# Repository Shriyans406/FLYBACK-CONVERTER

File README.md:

# Active-Clamp Flyback Converter (400 V → 54 V / 1 A)

Everything for this project lives in this one folder. There is one copy of each file.

## 1. What is where

| Path | What it is |
|---|---|
| `11-07-26.asc` | **The final LTspice design** (active-clamp flyback, closed loop) |
| `11-07-26.plt` | Plot layout LTspice loads automatically for that file |
| `11-07-26_RCD_original.asc` | Your original RCD-snubber version, kept as the only backup of it |
| `ACF_verification.png` | Waveform plots from the verified simulation |
| other `.asc` / `Draft*` files | Your earlier internship iterations (untouched) |
| `pcb/ACF_Flyback.kicad_pro` | **KiCad project — open this one** |
| `pcb/ACF_Flyback.kicad_sch` | Schematic |
| `pcb/ACF_Flyback.kicad_pcb` | Routed 2-layer board |
| `pcb/ACF_Flyback.kicad_dru` | High-voltage spacing rules used by the design-rule check |
| `pcb/ACF.kicad_sym`, `pcb/sym-lib-table` | Schematic symbols used by this project |
| `pcb/design.py` | **The single source of truth**: parts, values, positions, nets, spacing rules, copper pours |
| `pcb/gen_schematic.py`, `build_1_place.py`, `route.py`, `build_3_finish.py`, `make_bom.py` | Scripts that turn `design.py` into the schematic, board and BOM |
| `pcb/build_all.bat` | Runs all of the above in order |
| `pcb/check_netlist.py` | Cross-checks the schematic netlist against `design.py` |
| `pcb/pads.json`, `pcb/routes.json` | Intermediate data passed between the build scripts |
| `pcb/fab/gerbers/` | Gerber + drill files for the PCB manufacturer |
| `pcb/fab/ACF_Flyback_BOM.csv` | Bill of materials |
| `pcb/fab/ACF_Flyback_CPL.csv` | Pick-and-place (component position) file |
| `pcb/fab/ACF_Flyback_schematic.pdf` | Schematic as a PDF |
| `pcb/fab/DRC_report.txt`, `ERC_report.txt` | Board and schematic check reports |
| `pcb/renders/top.png`, `bottom.png` | 3D renders of the board |

### Usability features on the board (converter values unchanged)

| Feature | Where | What it is for |
|---|---|---|
| **HV LIVE** red LED (`D3`, `R26`–`R28`) | primary, left of centre | Lit while the bulk capacitor is charged. Do not touch the board until it goes out. Draws about 0.6 mA from the 400 V rail. |
| **BIAS** yellow LED (`D4`, `R25`) | next to the 12 V header | Shows the controller supply is present. |
| **OUTPUT ON** green LED (`D5`, `R24`) | secondary, lower right | Shows 54 V is present. Draws about 2 mA. |
| Probe loops `TP1` VOUT, `TP2` RTN | secondary, lower right | Clip a multimeter or scope here to measure the output safely. |
| Probe points `TP3` VCC, `TP4` PGND, `TP5` CS, `TP6` GATE | primary | Debug points. **These are on the live side: use an isolated or differential probe.** |
| Silkscreen legends | at every connector, LED and test point | Polarity (`+400V`/`GND`, `+54V`/`RTN`), fuse rating, bias pin order, and a discharge warning. |
| Rounded corners (3 mm) | board outline | Safer handling, easier fit in a case. |
| Fiducials `FID1`–`FID3` | three corners | Alignment marks for machine assembly. |
| Enclosure | `pcb/enclosure/` | 163 × 108 × 51 mm tray with stand-offs under the four M3 holes, wire openings at both terminal blocks and the bias header, and a flat lid. |

Enclosure files: `ACF_enclosure_base.wrl` / `_lid.wrl` are what KiCad's 3D viewer shows; `ACF_enclosure_base.stl` / `_lid.stl` are the same shapes in millimetres for CAD or 3D printing. `gen_enclosure.py` creates them from the `ENC` settings in `design.py`.

To see the enclosure in KiCad: open the board, press **Alt+3**. The base is shown; the lid is hidden so it does not cover the board. To show the lid, double-click footprint `ENC2` (select it via **Edit → Find**, search `ENC2`), go to the **3D Models** tab and tick **Show**. To hide the whole case, untick **Show** on `ENC1` the same way. The case outline is also drawn on the `User.Drawings` layer.

## 2. How to view everything

### LTspice simulation
1. Double-click `11-07-26.asc` (opens in LTspice).
2. Press the **Run** button (running man). The run takes about 2 minutes.
3. Four plots appear automatically: `V(out)`, `V(ds)`, `I(L1)`, and duty/soft-start.
4. Click any wire to plot its voltage; click a component to plot its current.
5. **View → SPICE Output Log** (Ctrl+L) shows the measured numbers: output voltage, ripple, efficiency, duty, peak `V(ds)`, and `V(ds)` at turn-on (the zero-voltage-switching check).
6. To see zero-voltage switching: zoom into the last few cycles and plot `V(ds)` together with `V(gs)`.

The `.raw` result file is about 430 MB, so it was deleted to save space. LTspice recreates it each time you press Run.

### KiCad schematic and board
1. Open **KiCad**, then **File → Open Project** and pick `pcb/ACF_Flyback.kicad_pro`.
2. Double-click the schematic file to open the **Schematic Editor**. The sheet is split into six numbered sections. Every pin carries a net label instead of drawn wires; pins with the same label are connected. Click a label and press **`** (backtick) to highlight that net.
3. Double-click the board file to open the **PCB Editor**.
   - **View → 3D Viewer** (Alt+3) shows the board in 3D.
   - Use the layer list on the right to show only `F.Cu` (top copper) or `B.Cu` (bottom copper).
   - Click any pad or track and press **`** to highlight its whole net.
   - **Inspect → Design Rules Checker → Run DRC** re-runs the check. Tick "Test for parity between PCB and schematic" to compare against the schematic.
4. Manufacturing files: in the KiCad project window choose **Gerber Viewer**, then **File → Open Gerber Job File** and pick `pcb/fab/gerbers/ACF_Flyback-job.gbrjob`. Then **File → Open Excellon Drill File** and pick `ACF_Flyback.drl`.
5. `BOM.csv` and `CPL.csv` open in Excel. The PDF and PNG files open with any viewer.

## 3. How to change things

### LTspice
- Right-click a component to change its value; right-click a blue text line to edit a directive.
- Useful knobs: `C1` (output capacitor), `L1`/`L2` (transformer, keep the 100:1 inductance ratio for 10:1 turns), `Cclamp`, `R2`/`C2`/`C3` (compensator), `Vss` (soft-start ramp), `Istep` (load step; delete it for a plain steady-state run).
- `.options reltol=0.001` gives clean waveforms. Changing it to `0.01` runs about 3× faster but adds a fake low-frequency wobble.

### PCB — two ways, do not mix them
**A. Edit by hand in KiCad** (best for small moves or re-routing):
edit the schematic or board in KiCad and save. Then use **Tools → Update PCB from Schematic** as normal.
Do **not** run `build_all.bat` afterwards — it regenerates the files and overwrites hand edits.

**B. Edit `pcb/design.py` and regenerate** (best for changing parts, values, positions or spacing rules):
1. Close KiCad (it locks the files).
2. Open `pcb/design.py` in any text editor.
   - `PARTS` — one line per component: footprint, value, x/y position in mm, rotation, and which pad goes to which net.
   - `clearance()` — the spacing rules between voltage domains.
   - `POURS` — the copper pour rectangles.
   - `TRACK_W` — track widths per net.
3. Double-click `pcb/build_all.bat`. It takes about 2 minutes.
4. Read `pcb/fab/DRC_report.txt` and `pcb/fab/ERC_report.txt`, then open the project in KiCad to look.

If the router prints `FAILED` for a net, two parts are too close for the spacing rules: move one of them in `PARTS` and run again.

## 4. How it was built

### Simulation
1. Read the internship report and the original `11-07-26.asc` (RCD-snubber flyback).
2. Replaced the RCD snubber with an active clamp (clamp MOSFET `M2` + `Cclamp`), driven complementary to `M1` with 0.5 µs dead-time.
3. Raised the transformer inductance from 572 µH to 25 mH so the magnetising current swings negative each cycle. That is what gives zero-voltage switching and removes the idle period that caused ringing.
4. Replaced the generic MOSFET with a model of the Infineon IMBF170R1K0M1, fitted to its datasheet values.
5. Recalculated the output capacitor for the new operating point (180 µF) and retuned the compensator.
6. Added a duty soft-start and an anti-windup clamp on the error amplifier.
7. Ran LTspice in batch mode after each change and read the `.meas` results until output voltage, ripple, zero-voltage switching and a load step all checked out.

### PCB
1. Chose real parts for what LTspice modelled as ideal blocks: LM5025 controller, UCC5350 isolated high-side driver with bootstrap diode, TL431 + optocoupler feedback, fuse, bulk capacitor, Y capacitor.
2. Wrote the whole design as data in `design.py`.
3. `build_1_place.py` (KiCad's Python) creates the board outline and isolation slots and places every footprint from the KiCad libraries.
4. `route.py` is a grid router written for this board. It routes each net on a 0.1 mm grid and keeps the spacing each voltage domain needs.
5. `build_3_finish.py` adds the tracks, vias, thermal vias, copper pours and bottom-side high-voltage keep-outs, fills the zones, and writes the DRC rule file.
6. `gen_schematic.py` writes the schematic from the same data, so the schematic and board cannot disagree.
7. KiCad's own checks were then run from the command line: DRC with schematic parity, and ERC. Result: 0 errors, 0 unconnected nets, 0 parity issues, 14 silkscreen warnings.
8. Gerbers, drill, placement, BOM, PDF and renders were exported with `kicad-cli`.

## 5. Known limits — read before ordering boards

- **Transformer footprint is a placeholder** (library ETD29 bobbin). A 25 mH, 10 kHz transformer needs a larger core; replace the footprint once the transformer is designed.
- **10 kHz is unusually low for the LM5025**; check its oscillator range or raise the switching frequency.
- **MOSFET footprint is the generic TO-263-7 pattern**; check it against Infineon's package drawing.
- **Spacing values are engineering choices** (8 mm primary-to-secondary, 3 mm around 1 kV nets, 2.5 mm around 400 V), not checked against a specific safety standard. 3 mm at 1 kV assumes conformal coating.
- **The TL431/optocoupler loop values are starting points**; that loop was not simulated.
- **Pin assumptions to check on datasheets:** LM5025 VIN tied to VCC for 12 V operation; TL431 pin order for the vendor you buy.
- **The BOM has no manufacturer part numbers for passives**, and the placement file includes through-hole parts.
- **Controller bias is an external 12 V header**, not an auxiliary winding.
- **The enclosure is a concept model.** It is plain blocks: no screw holes in the stand-offs, no lid fixings, no vents, and its 38 mm inner height has not been checked against a real transformer. The STL files are overlapping solids and have not been test-printed. Choose a flame-rated insulating material for a 400 V product.
- **The two indicator LEDs on the power rails add small loads** (about 0.6 mA at 400 V and 2 mA at 54 V); these were not added to the LTspice model.

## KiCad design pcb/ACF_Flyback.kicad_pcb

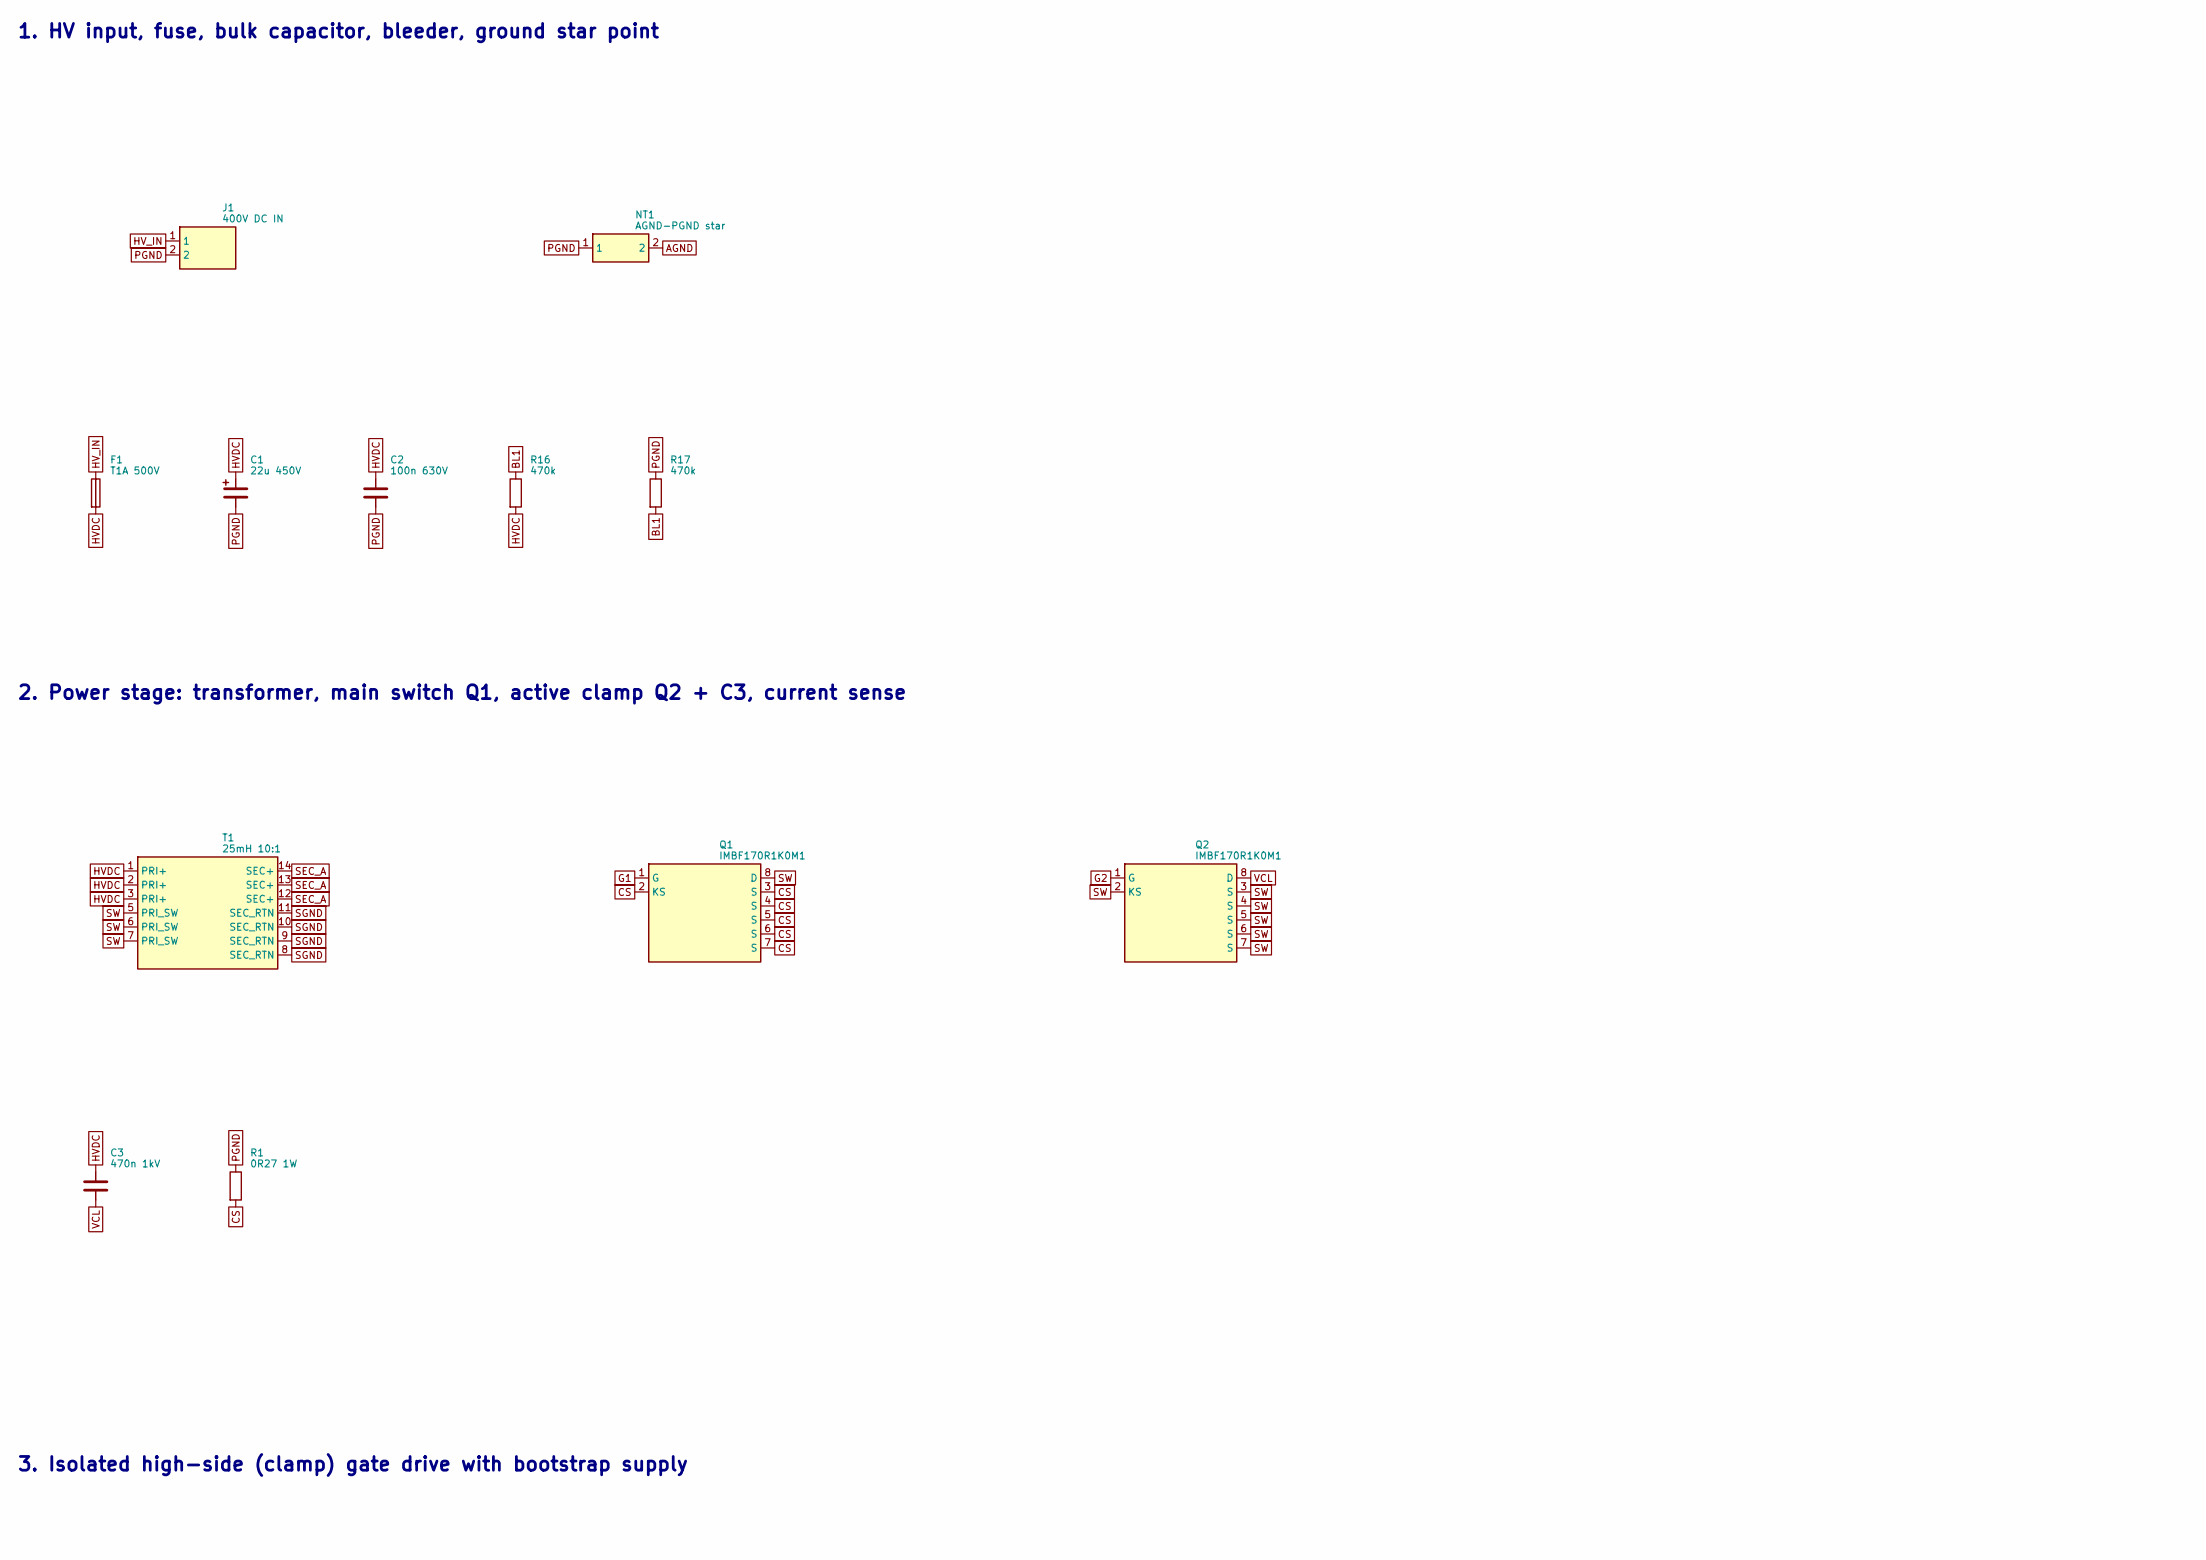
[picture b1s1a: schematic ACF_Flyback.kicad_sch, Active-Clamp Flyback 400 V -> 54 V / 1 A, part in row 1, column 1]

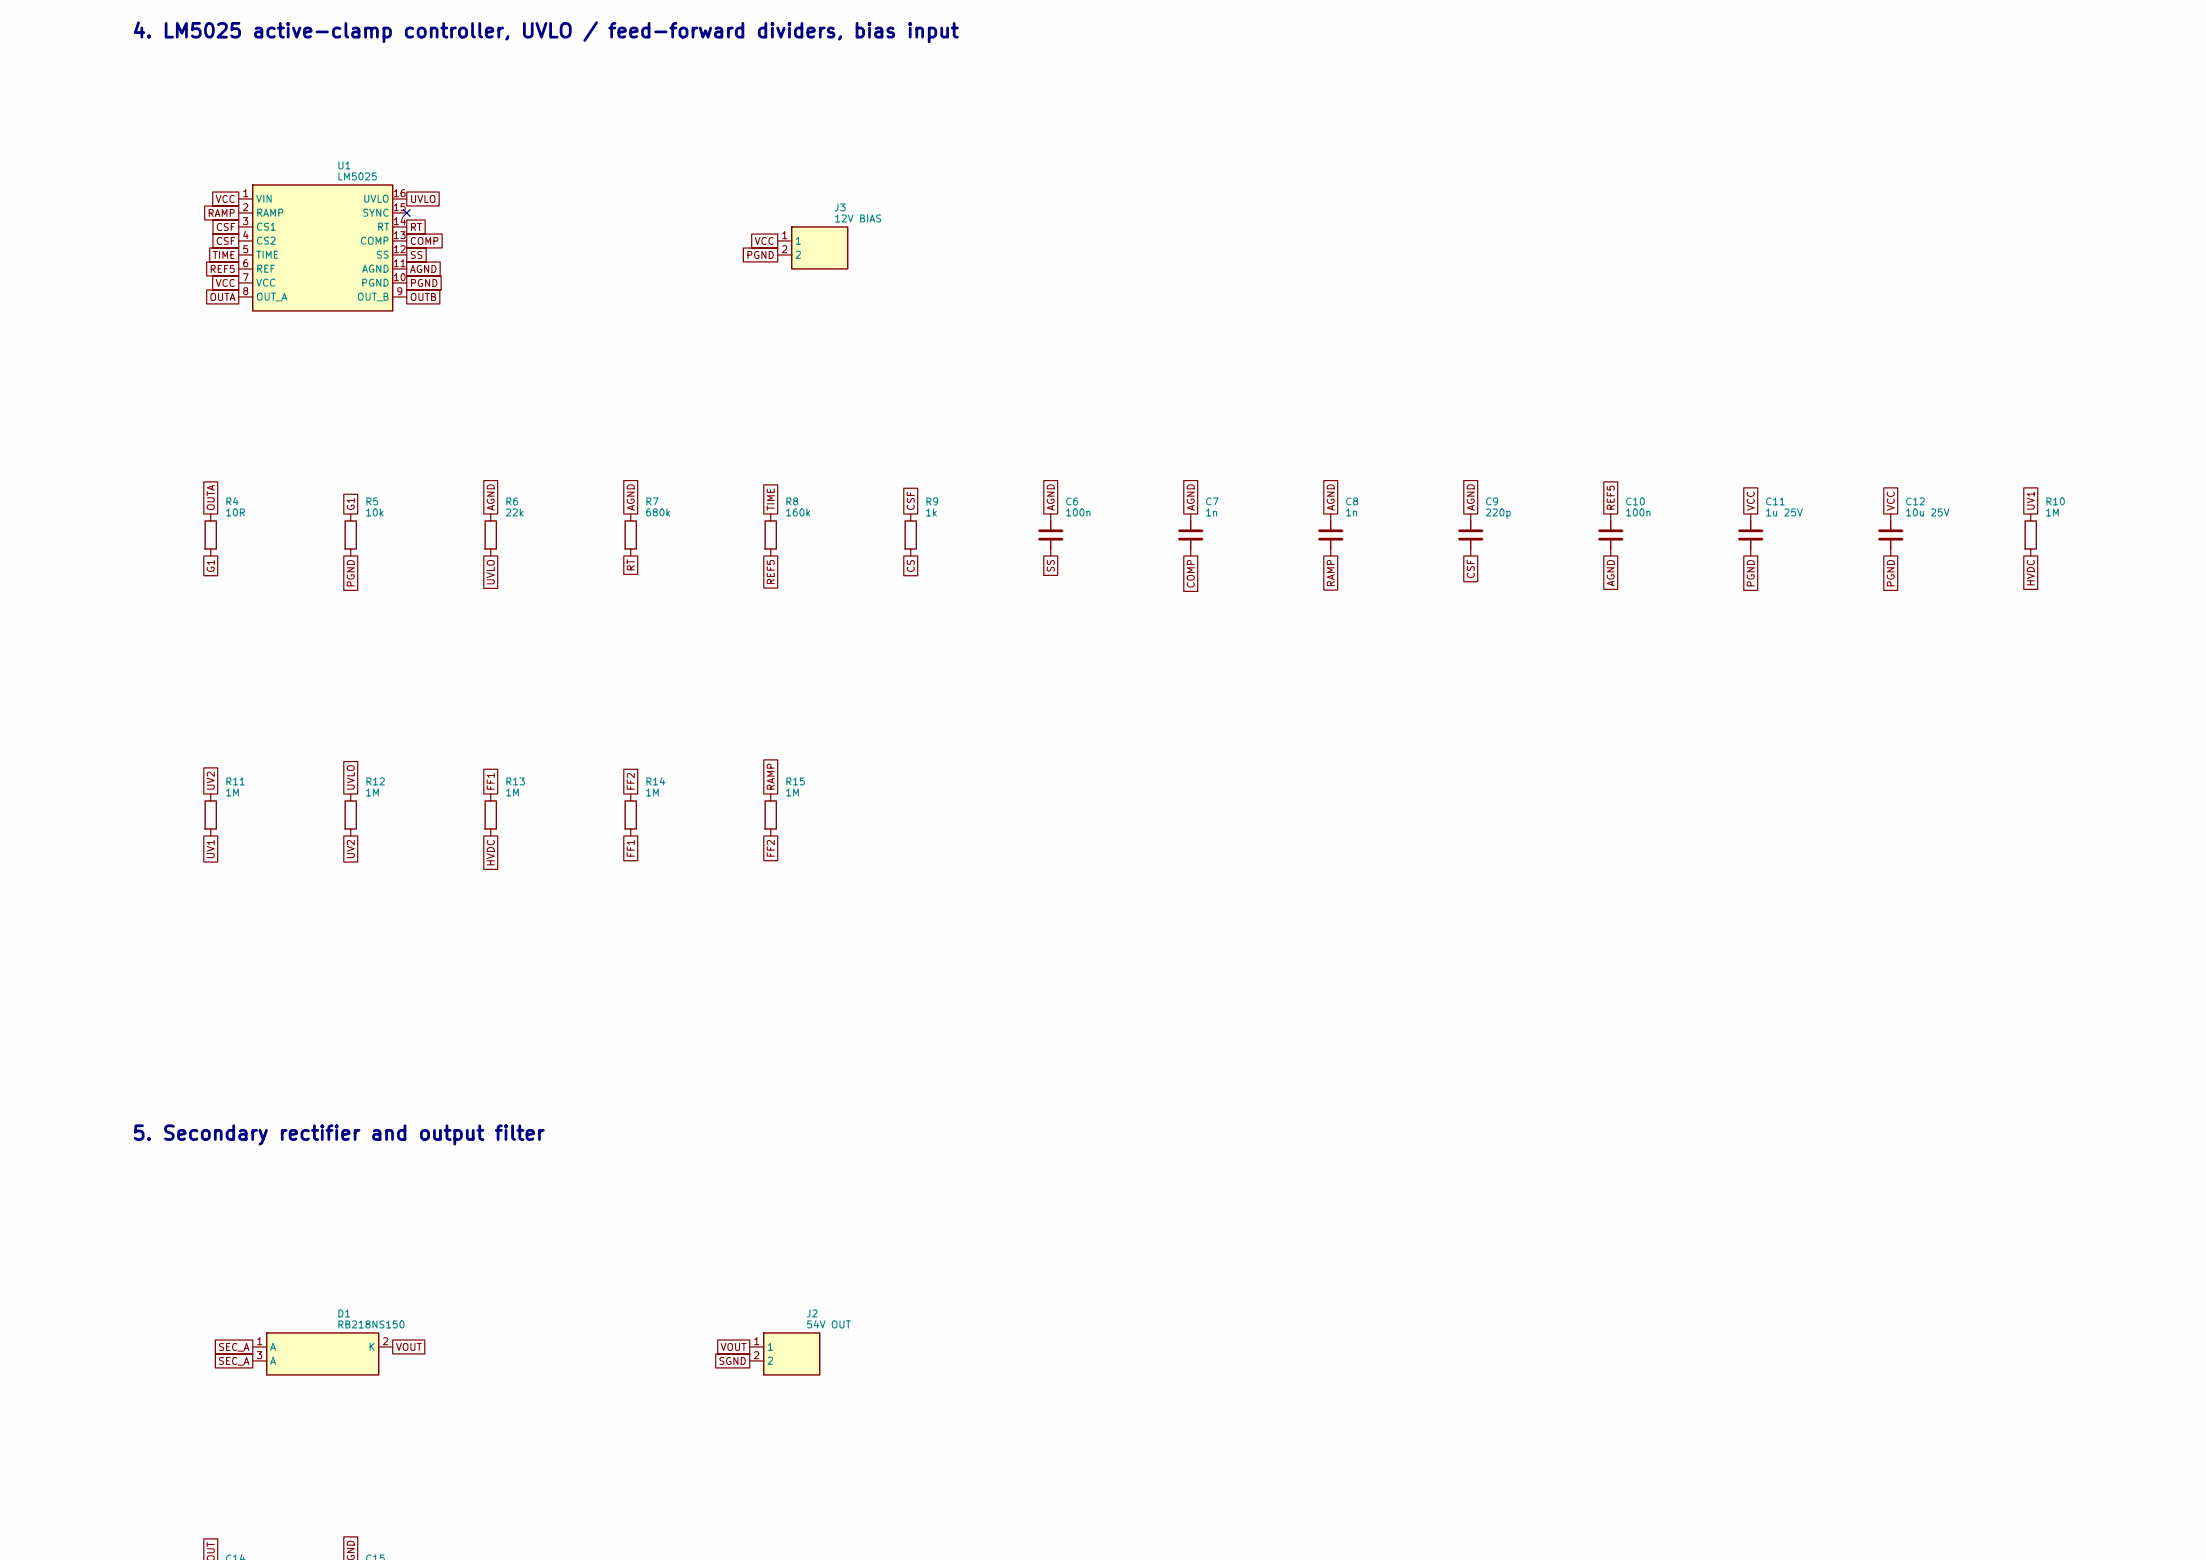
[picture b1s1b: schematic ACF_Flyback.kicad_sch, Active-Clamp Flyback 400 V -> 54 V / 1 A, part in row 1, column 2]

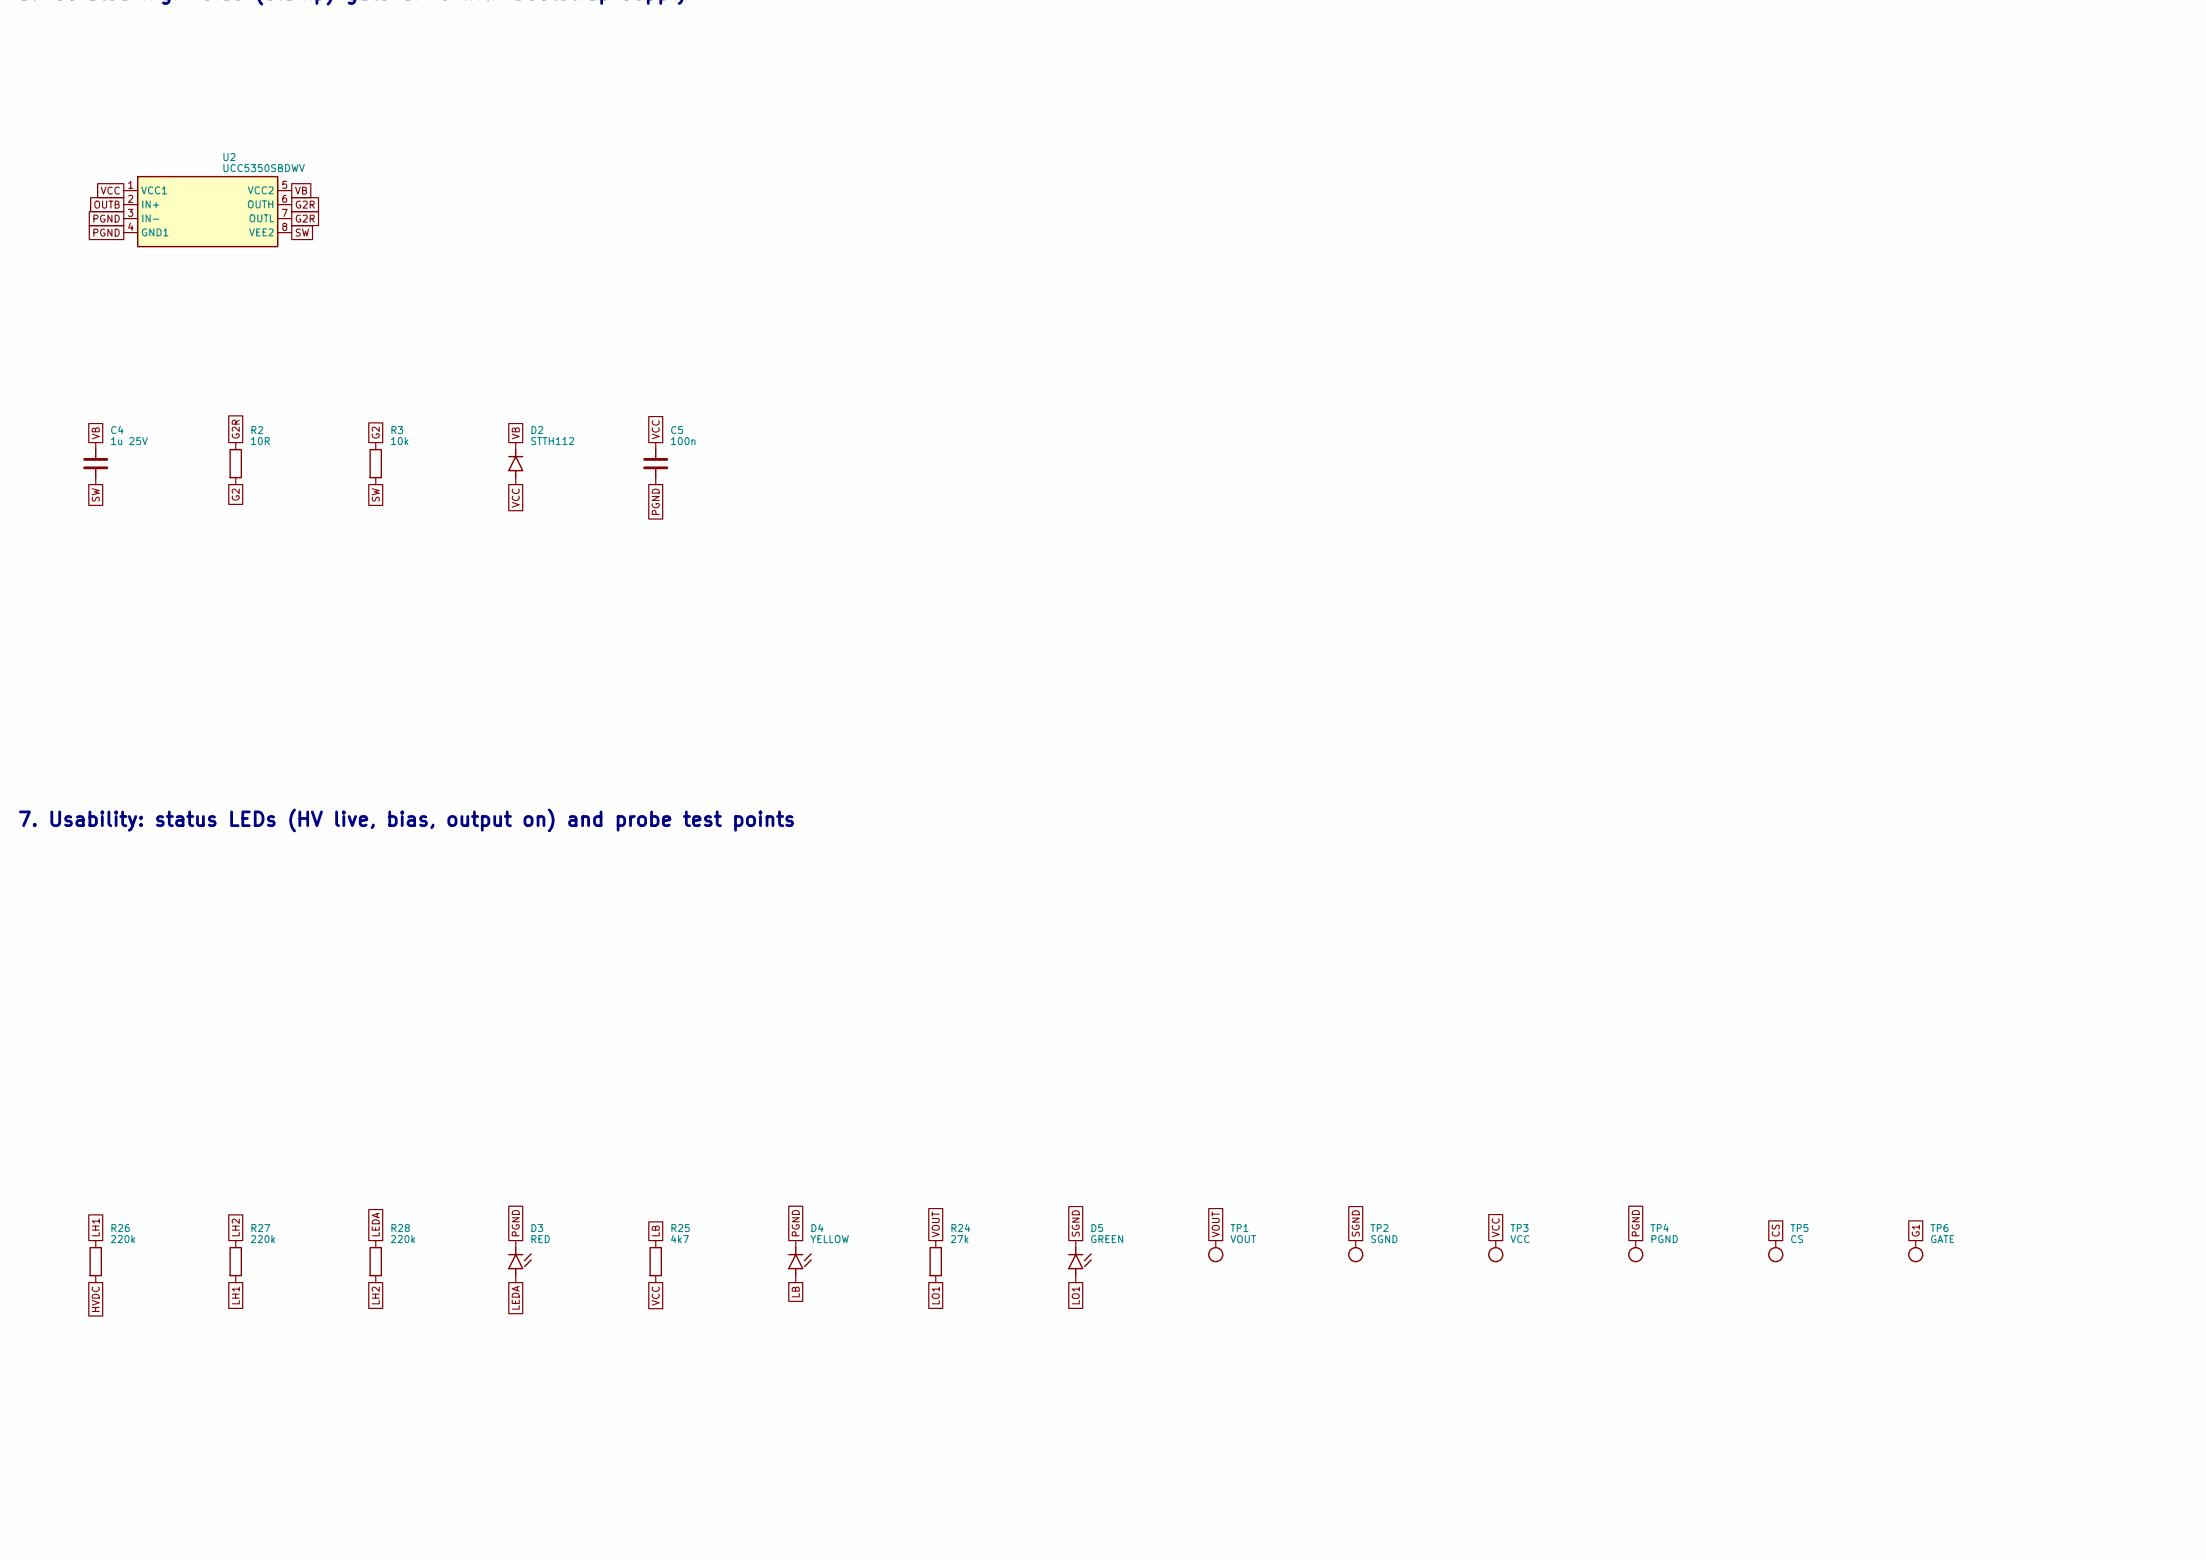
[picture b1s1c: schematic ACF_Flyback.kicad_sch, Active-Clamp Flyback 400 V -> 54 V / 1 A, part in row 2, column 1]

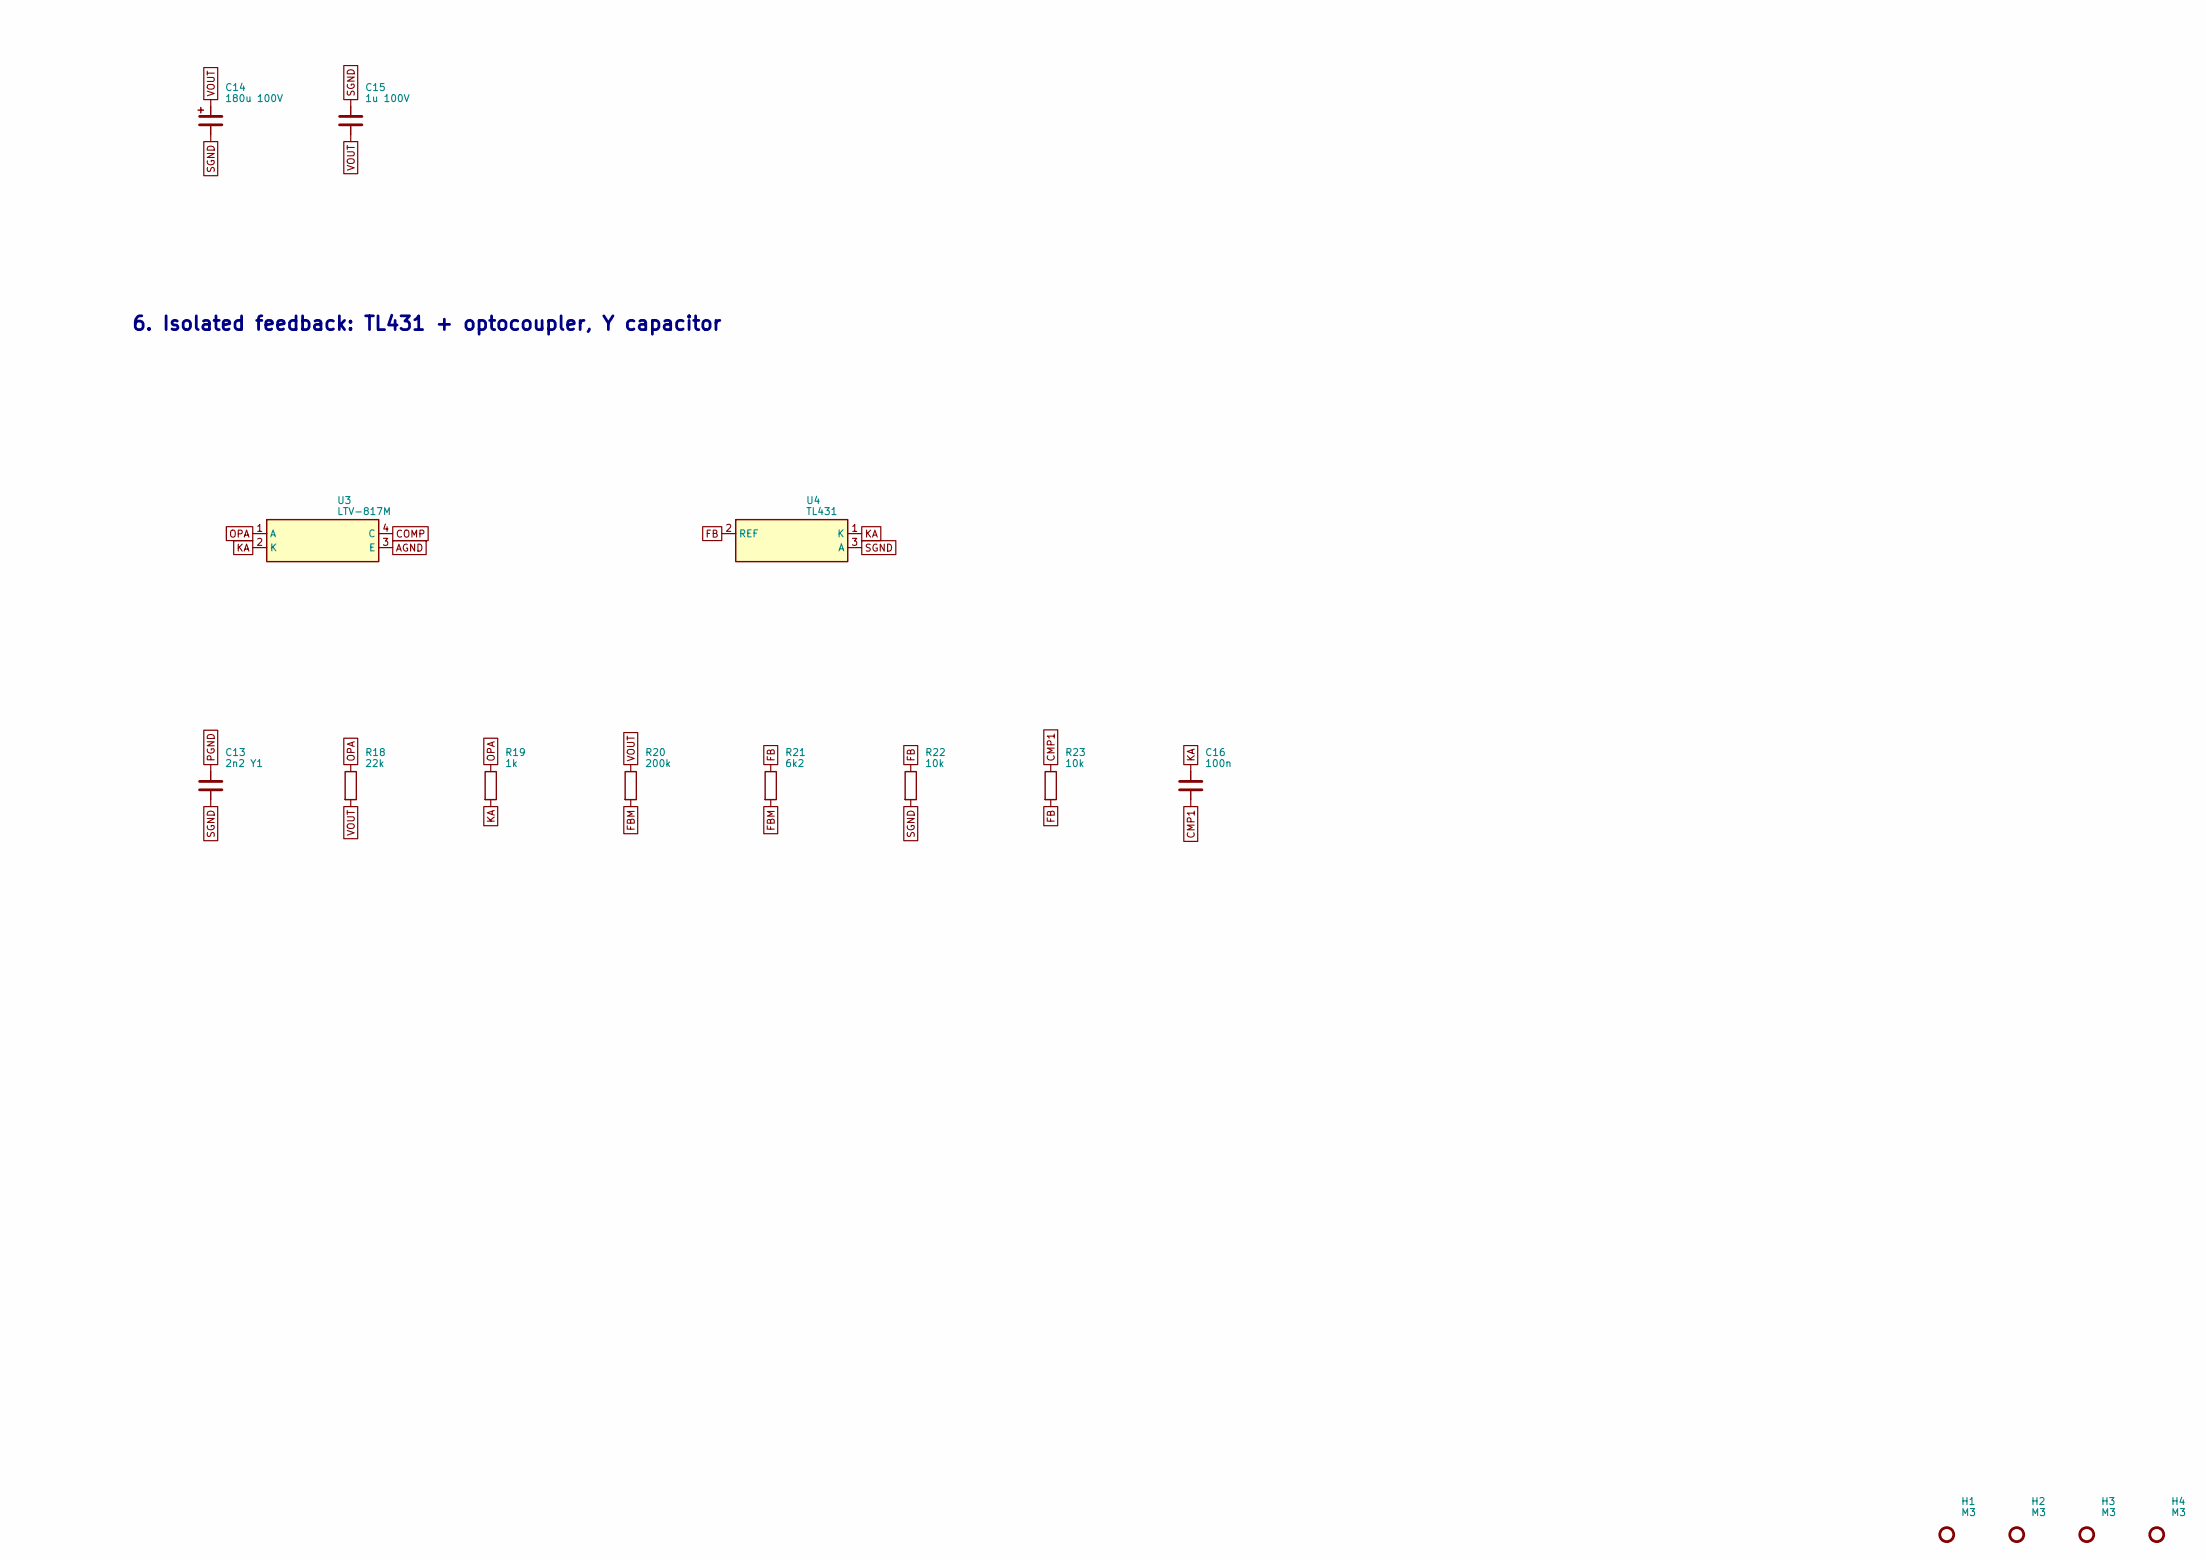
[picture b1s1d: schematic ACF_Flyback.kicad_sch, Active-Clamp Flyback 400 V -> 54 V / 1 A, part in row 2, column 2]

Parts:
C1: 22u 450V; CP_Radial_D12.5mm_P5.00mm
C2: 100n 630V; C_Rect_L13.0mm_W5.0mm_P10.00mm_FKS3_FKP3_MKS4
C3: 470n 1kV; C_Rect_L31.5mm_W9.0mm_P27.50mm_MKS4
C4, C11: 1u 25V; C_0805_2012Metric
C5, C6, C10, C16: 100n; C_0805_2012Metric
C7, C8: 1n; C_0805_2012Metric
C9: 220p; C_0805_2012Metric
C12: 10u 25V; C_1206_3216Metric
C13: 2n2 Y1; C_Disc_D11.0mm_W5.0mm_P10.00mm
C14: 180u 100V; CP_Radial_D12.5mm_P5.00mm
C15: 1u 100V; C_1210_3225Metric
D1: RB218NS150; TO-263-2
D2: STTH112; D_DO-41_SOD81_P10.16mm_Horizontal
D3: RED; LED_0805_2012Metric
D4: YELLOW; LED_0805_2012Metric
D5: GREEN; LED_0805_2012Metric
F1: T1A 500V; Fuseholder_Clip-5x20mm_Keystone_3517_Inline_P23.11x6.76mm_D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
H1, H2, H3, H4: M3; MountingHole_3.2mm_M3
J1: 400V DC IN; TerminalBlock_Phoenix_MKDS-3-2-5.08_1x02_P5.08mm_Horizontal
J2: 54V OUT; TerminalBlock_Phoenix_MKDS-1,5-2-5.08_1x02_P5.08mm_Horizont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
J3: 12V BIAS; PinHeader_1x02_P2.54mm_Vertical
NT1: AGND-PGND star; NetTie-2_SMD_Pad0.5mm
Q1, Q2: IMBF170R1K0M1; TO-263-7_TabPin8
R1: 0R27 1W; R_2512_6332Metric
R2: 10R; R_1206_3216Metric
R3, R5, R22, R23: 10k; R_0805_2012Metric
R4: 10R; R_0805_2012Metric
R6: 22k; R_0805_2012Metric
R7: 680k; R_0805_2012Metric
R8: 160k; R_0805_2012Metric
R9, R19: 1k; R_0805_2012Metric
R10, R11, R12, R13, R14, R15: 1M; R_1206_3216Metric
R16, R17: 470k; R_1206_3216Metric
R18: 22k; R_1206_3216Metric
R20: 200k; R_1206_3216Metric
R21: 6k2; R_0805_2012Metric
R24: 27k; R_1206_3216Metric
R25: 4k7; R_0805_2012Metric
R26, R27, R28: 220k; R_1206_3216Metric
T1: 25mH 10:1; Transformer_EPCOS_B66359A1013T_Horizontal
TP1: VOUT; TestPoint_Loop_D2.50mm_Drill1.0mm
TP2: SGND; TestPoint_Loop_D2.50mm_Drill1.0mm
TP3: VCC; TestPoint_Pad_D2.0mm
TP4: PGND; TestPoint_Loop_D2.50mm_Drill1.0mm
TP5: CS; TestPoint_Pad_D2.0mm
TP6: GATE; TestPoint_Pad_D2.0mm
U1: LM5025; TSSOP-16_4.4x5mm_P0.65mm
U2: UCC5350SBDWV; SOIC-8_7.5x5.85mm_P1.27mm
U3: LTV-817M; DIP-4_W10.16mm
U4: TL431; SOT-23

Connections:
AGND: C6.1, C7.1, C8.1, C9.1, C10.2, NT1.2, R6.1, R7.1, U1.11 (AGND), U3.3 (E)
BL1: R16.1, R17.2
CMP1: C16.2, R23.1
COMP: C7.2, U1.13 (COMP), U3.4 (C)
CS: Q1.2 (KS), Q1.3 (S), Q1.4 (S), Q1.5 (S), Q1.6 (S), Q1.7 (S), R1.2, R9.2, TP5.1
CSF: C9.2, R9.1, U1.3 (CS1), U1.4 (CS2)
FB: R21.1, R22.1, R23.2, U4.2 (REF)
FBM: R20.2, R21.2
FF1: R13.1, R14.2
FF2: R14.1, R15.2
G1: Q1.1 (G), R4.2, R5.1, TP6.1
G2: Q2.1 (G), R2.2, R3.1
G2R: R2.1, U2.6 (OUTH), U2.7 (OUTL)
HVDC: C1.1, C2.1, C3.1, F1.2, R10.2, R13.2, R16.2, R26.2, T1.1 (PRI+), T1.2 (PRI+), T1.3 (PRI+)
HV_IN: F1.1, J1.1
KA: C16.1, R19.2, U3.2 (K), U4.1 (K)
LB: D4.2, R25.1
LEDA: D3.2, R28.1
LH1: R26.1, R27.2
LH2: R27.1, R28.2
LO1: D5.2, R24.2
OPA: R18.1, R19.1, U3.1 (A)
OUTA: R4.1, U1.8 (OUT_A)
OUTB: U1.9 (OUT_B), U2.2 (IN+)
PGND: C1.2, C2.2, C5.2, C11.2, C12.2, C13.1, D3.1, D4.1, J1.2, J3.2, NT1.1, R1.1, R5.2, R17.1, TP4.1, U1.10 (PGND), U2.3 (IN-), U2.4 (GND1)
RAMP: C8.2, R15.1, U1.2 (RAMP)
REF5: C10.1, R8.2, U1.6 (REF)
RT: R7.2, U1.14 (RT)
SEC_A: D1.1 (A), D1.3 (A), T1.12 (SEC+), T1.13 (SEC+), T1.14 (SEC+)
SGND: C13.2, C14.2, C15.1, D5.1, J2.2, R22.2, T1.8 (SEC_RTN), T1.9 (SEC_RTN), T1.10 (SEC_RTN), T1.11 (SEC_RTN), TP2.1, U4.3 (A)
SS: C6.2, U1.12 (SS)
SW: C4.2, Q1.8 (D), Q2.2 (KS), Q2.3 (S), Q2.4 (S), Q2.5 (S), Q2.6 (S), Q2.7 (S), R3.2, T1.5 (PRI_SW), T1.6 (PRI_SW), T1.7 (PRI_SW), U2.8 (VEE2)
TIME: R8.1, U1.5 (TIME)
UV1: R10.1, R11.2
UV2: R11.1, R12.2
UVLO: R6.2, R12.1, U1.16 (UVLO)
VB: C4.1, D2.1, U2.5 (VCC2)
VCC: C5.1, C11.1, C12.1, D2.2, J3.1, R25.2, TP3.1, U1.1 (VIN), U1.7 (VCC), U2.1 (VCC1)
VCL: C3.2, Q2.8 (D)
VOUT: C14.1, C15.2, D1.2 (K), J2.1, R18.2, R20.1, R24.1, TP1.1

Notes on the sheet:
1. HV input, fuse, bulk capacitor, bleeder, ground star point
2. Power stage: transformer, main switch Q1, active clamp Q2 + C3, current sense
3. Isolated high-side (clamp) gate drive with bootstrap supply
4. LM5025 active-clamp controller, UVLO / feed-forward dividers, bias input
5. Secondary rectifier and output filter
6. Isolated feedback: TL431 + optocoupler, Y capacitor
7. Usability: status LEDs (HV live, bias, output on) and probe test points

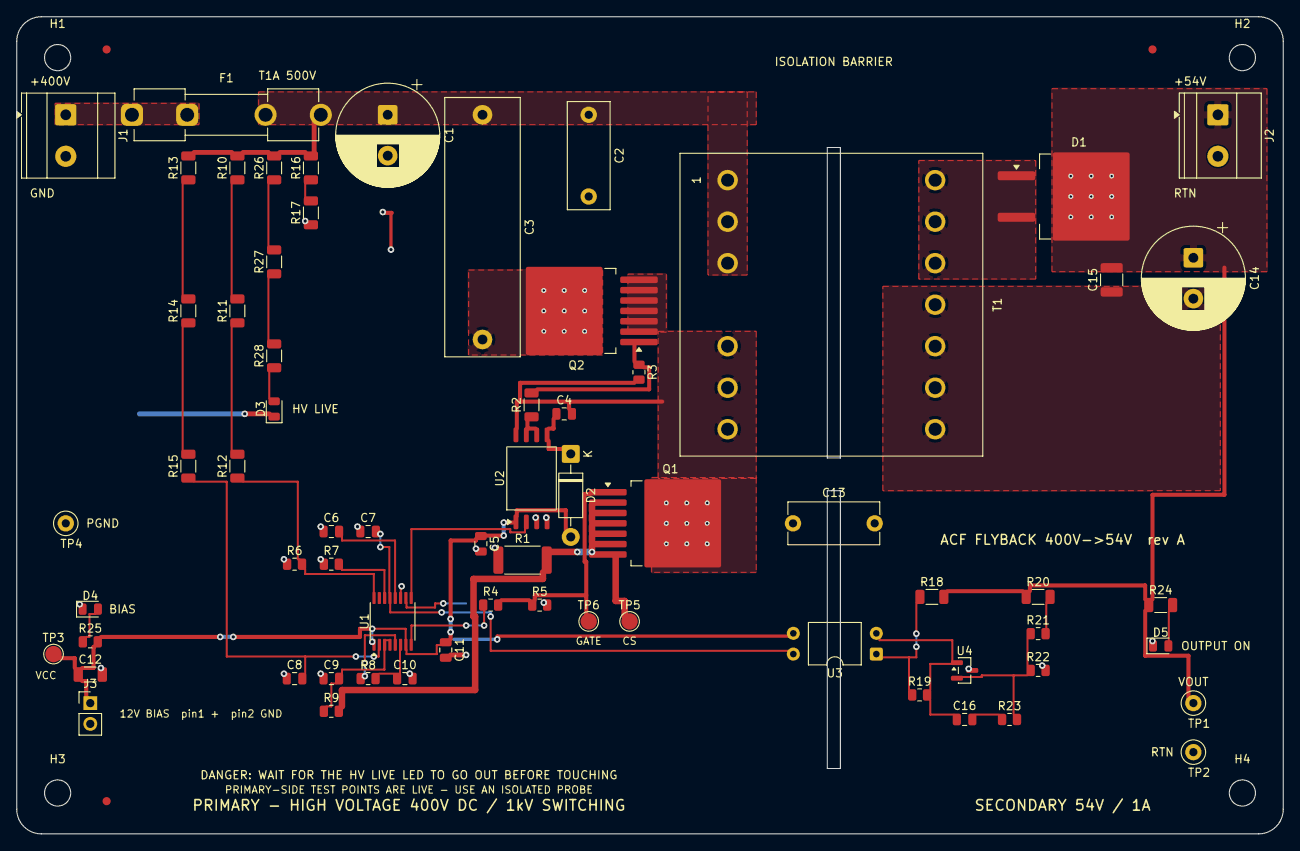
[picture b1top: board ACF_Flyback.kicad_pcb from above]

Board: 2 copper layers, 155.0 x 100.0 mm, 76 parts (0 on the bottom side), 40 nets.

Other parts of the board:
ENC1: Enclosure base
ENC2: Enclosure lid
FID1, FID2, FID3: Fiducial; Fiducial_1mm_Mask2mm

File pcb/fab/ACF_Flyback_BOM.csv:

Qty,References,Value,Footprint,Description
1,J1,400V DC IN,TerminalBlock_Phoenix_MKDS-3-2-5.08_1x02_P5.08mm_Horizontal,"Phoenix MKDS 3/2-5,08"
1,F1,T1A 500V,Fuseholder_Clip-5x20mm_Keystone_3517_Inline_P23.11x6.76mm_D1.70mm_Horizontal,Keystone 3517 clips + 5x20 fuse
1,C1,22u 450V,CP_Radial_D12.5mm_P5.00mm,bulk electrolytic
1,C2,100n 630V,C_Rect_L13.0mm_W5.0mm_P10.00mm_FKS3_FKP3_MKS4,"film, HF loop bypass"
1,C3,470n 1kV,C_Rect_L31.5mm_W9.0mm_P27.50mm_MKS4,film clamp capacitor
1,T1,25mH 10:1,Transformer_EPCOS_B66359A1013T_Horizontal,PLACEHOLDER ETD29 bobbin - see notes
1,Q1,IMBF170R1K0M1,TO-263-7_TabPin8,"Infineon 1700V SiC, main switch"
1,Q2,IMBF170R1K0M1,TO-263-7_TabPin8,"Infineon 1700V SiC, clamp switch"
1,R1,0R27 1W,R_2512_6332Metric,current sense
1,U2,UCC5350SBDWV,SOIC-8_7.5x5.85mm_P1.27mm,isolated high-side gate driver
1,C4,1u 25V,C_0805_2012Metric,bootstrap capacitor
1,R2,10R,R_1206_3216Metric,Q2 gate resistor
1,R3,10k,R_0805_2012Metric,Q2 gate pull-down
1,D2,STTH112,D_DO-41_SOD81_P10.16mm_Horizontal,1200V bootstrap diode
1,C5,100n,C_0805_2012Metric,U2 input decoupling
1,R4,10R,R_0805_2012Metric,Q1 gate resistor
1,R5,10k,R_0805_2012Metric,Q1 gate pull-down
1,U1,LM5025,TSSOP-16_4.4x5mm_P0.65mm,active-clamp PWM controller
1,R6,22k,R_0805_2012Metric,UVLO divider bottom
1,R7,680k,R_0805_2012Metric,"oscillator (10 kHz, see notes)"
1,C6,100n,C_0805_2012Metric,soft-start
1,C7,1n,C_0805_2012Metric,COMP noise filter
1,C8,1n,C_0805_2012Metric,ramp capacitor
1,C9,220p,C_0805_2012Metric,current-sense filter
1,R8,160k,R_0805_2012Metric,dead-time set
1,C10,100n,C_0805_2012Metric,REF decoupling
1,R9,1k,R_0805_2012Metric,current-sense filter
1,C11,1u 25V,C_0805_2012Metric,VCC decoupling
1,C12,10u 25V,C_1206_3216Metric,VCC bulk
1,J3,12V BIAS,PinHeader_1x02_P2.54mm_Vertical,primary-referenced 12 V bias input
3,R10 R11 R12,1M,R_1206_3216Metric,UVLO divider
3,R13 R14 R15,1M,R_1206_3216Metric,ramp feed-forward
2,R16 R17,470k,R_1206_3216Metric,bulk bleeder
1,C13,2n2 Y1,C_Disc_D11.0mm_W5.0mm_P10.00mm,Y1 safety capacitor
1,U3,LTV-817M,DIP-4_W10.16mm,"optocoupler, 10.16 mm lead form"
1,D1,RB218NS150,TO-263-2,150V 20A Schottky
1,C14,180u 100V,CP_Radial_D12.5mm_P5.00mm,"output electrolytic, low ESR"
1,C15,1u 100V,C_1210_3225Metric,output ceramic
1,J2,54V OUT,"TerminalBlock_Phoenix_MKDS-1,5-2-5.08_1x02_P5.08mm_Horizontal","Phoenix MKDS 1,5/2-5,08"
1,U4,TL431,SOT-23,shunt reference (check K/R/A pin order of chosen vendor)
1,R18,22k,R_1206_3216Metric,opto LED feed
1,R19,1k,R_0805_2012Metric,TL431 bias
1,R20,200k,R_1206_3216Metric,feedback divider top
1,R21,6k2,R_0805_2012Metric,feedback divider top
1,R22,10k,R_0805_2012Metric,feedback divider bottom
1,C16,100n,C_0805_2012Metric,Type-II compensation
1,R23,10k,R_0805_2012Metric,Type-II compensation
3,R26 R27 R28,220k,R_1206_3216Metric,HV-live LED dropper
1,D3,RED,LED_0805_2012Metric,HV LIVE indicator (bulk capacitor charged)
1,R25,4k7,R_0805_2012Metric,bias LED resistor
1,D4,YELLOW,LED_0805_2012Metric,12 V BIAS indicator
1,R24,27k,R_1206_3216Metric,output LED resistor
1,D5,GREEN,LED_0805_2012Metric,OUTPUT ON indicator
1,TP1,VOUT,TestPoint_Loop_D2.50mm_Drill1.0mm,"probe loop, +54 V output"
1,TP2,SGND,TestPoint_Loop_D2.50mm_Drill1.0mm,"probe loop, output return"
1,TP4,PGND,TestPoint_Loop_D2.50mm_Drill1.0mm,"probe loop, primary ground"

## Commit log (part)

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2026-06-06 started the first design
2026-06-06 design issues
2026-06-22 Simple Flyback
2026-06-22 Improved ckt with snubber and proper calc
2026-06-25 Not correct updated snubber ckt
